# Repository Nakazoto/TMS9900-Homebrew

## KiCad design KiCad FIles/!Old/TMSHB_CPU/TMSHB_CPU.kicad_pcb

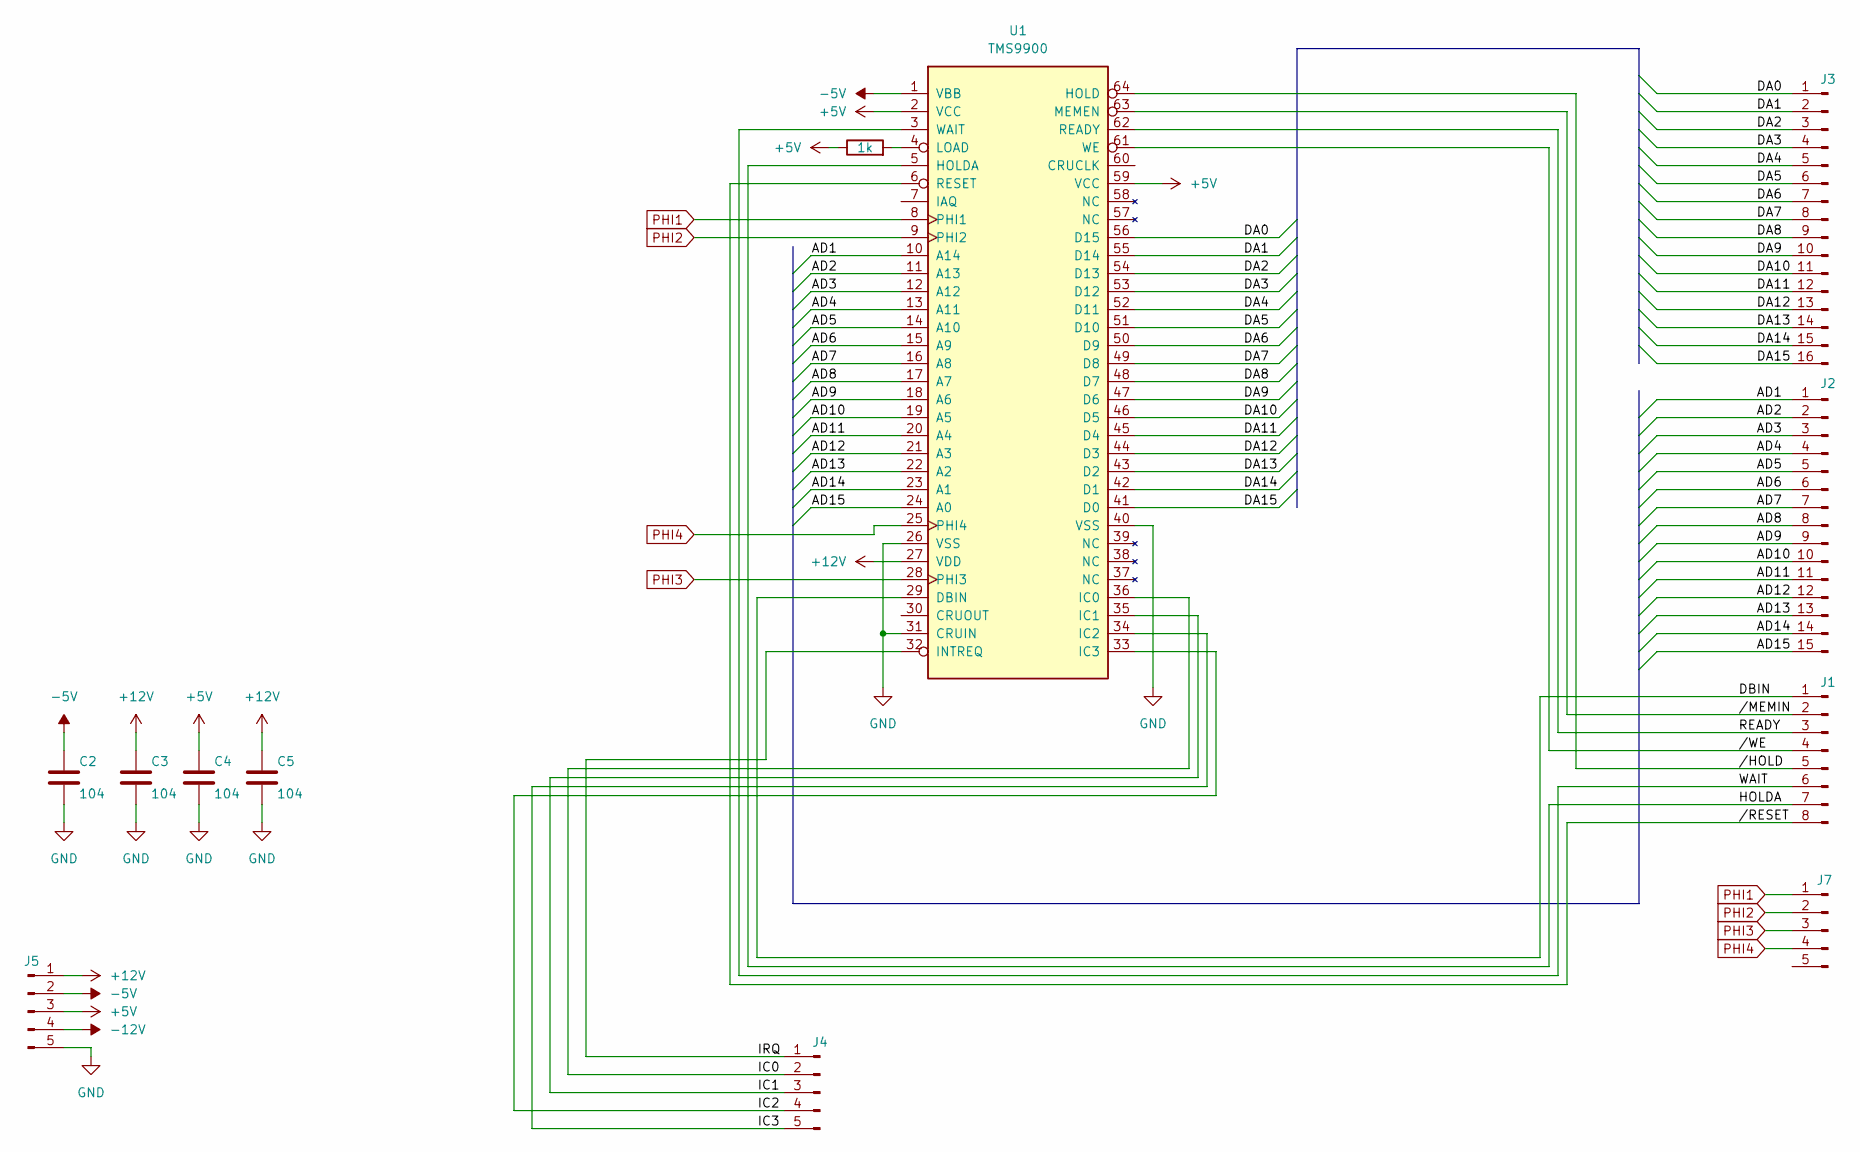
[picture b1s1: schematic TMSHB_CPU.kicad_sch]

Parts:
C2, C3, C4, C5: 104; C_Disc_D3.0mm_W2.0mm_P2.50mm
J1: Conn_01x08_Pin; PinHeader_1x08_P2.54mm_Vertical
J2: Conn_01x15_Pin; PinHeader_1x15_P2.54mm_Vertical
J3: Conn_01x16_Pin; PinHeader_1x16_P2.54mm_Vertical
J4, J5, J7: Conn_01x05_Pin; PinHeader_1x05_P2.54mm_Vertical
R1: 1k; R_Axial_DIN0207_L6.3mm_D2.5mm_P10.16mm_Horizontal
U1: TMS9900; DIP-64_W22.86mm

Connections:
+5V: C4.1, J5.3, R1.1, U1.2 (VCC), U1.59 (VCC)
+12V: C3.1, C5.1, J5.1, U1.27 (VDD)
-5V: C2.1, J5.2, U1.1 (VBB)
-12V: J5.4
/AD1: J2.1, U1.10 (A14)
/AD2: J2.2, U1.11 (A13)
/AD3: J2.3, U1.12 (A12)
/AD4: J2.4, U1.13 (A11)
/AD5: J2.5, U1.14 (A10)
/AD6: J2.6, U1.15 (A9)
/AD7: J2.7, U1.16 (A8)
/AD8: J2.8, U1.17 (A7)
/AD9: J2.9, U1.18 (A6)
/AD10: J2.10, U1.19 (A5)
/AD11: J2.11, U1.20 (A4)
/AD12: J2.12, U1.21 (A3)
/AD13: J2.13, U1.22 (A2)
/AD14: J2.14, U1.23 (A1)
/AD15: J2.15, U1.24 (A0)
/DA0: J3.1, U1.56 (D15)
/DA1: J3.2, U1.55 (D14)
/DA2: J3.3, U1.54 (D13)
/DA3: J3.4, U1.53 (D12)
/DA4: J3.5, U1.52 (D11)
/DA5: J3.6, U1.51 (D10)
/DA6: J3.7, U1.50 (D9)
/DA7: J3.8, U1.49 (D8)
/DA8: J3.9, U1.48 (D7)
/DA9: J3.10, U1.47 (D6)
/DA10: J3.11, U1.46 (D5)
/DA11: J3.12, U1.45 (D4)
/DA12: J3.13, U1.44 (D3)
/DA13: J3.14, U1.43 (D2)
/DA14: J3.15, U1.42 (D1)
/DA15: J3.16, U1.41 (D0)
/DBIN: J1.1, U1.29 (DBIN)
/HOLDA: J1.7, U1.5 (HOLDA)
/IC0: J4.2, U1.36 (IC0)
/IC1: J4.3, U1.35 (IC1)
/IC2: J4.4, U1.33 (IC3)
/IC3: J4.5, U1.34 (IC2)
/IRQ: J4.1, U1.32 (INTREQ)
/READY: J1.3, U1.62 (READY)
/WAIT: J1.6, U1.3 (WAIT)
//HOLD: J1.5, U1.64 (HOLD)
//MEMIN: J1.2, U1.63 (MEMEN)
//RESET: J1.8, U1.6 (RESET)
//WE: J1.4, U1.61 (WE)
GND: C2.2, C3.2, C4.2, C5.2, J5.5, U1.26 (VSS), U1.31 (CRUIN), U1.40 (VSS)
unnamed: R1.2, U1.4 (LOAD)
PHI1: J7.1, U1.8 (PHI1)
PHI2: J7.2, U1.9 (PHI2)
PHI3: J7.3, U1.28 (PHI3)
PHI4: J7.4, U1.25 (PHI4)

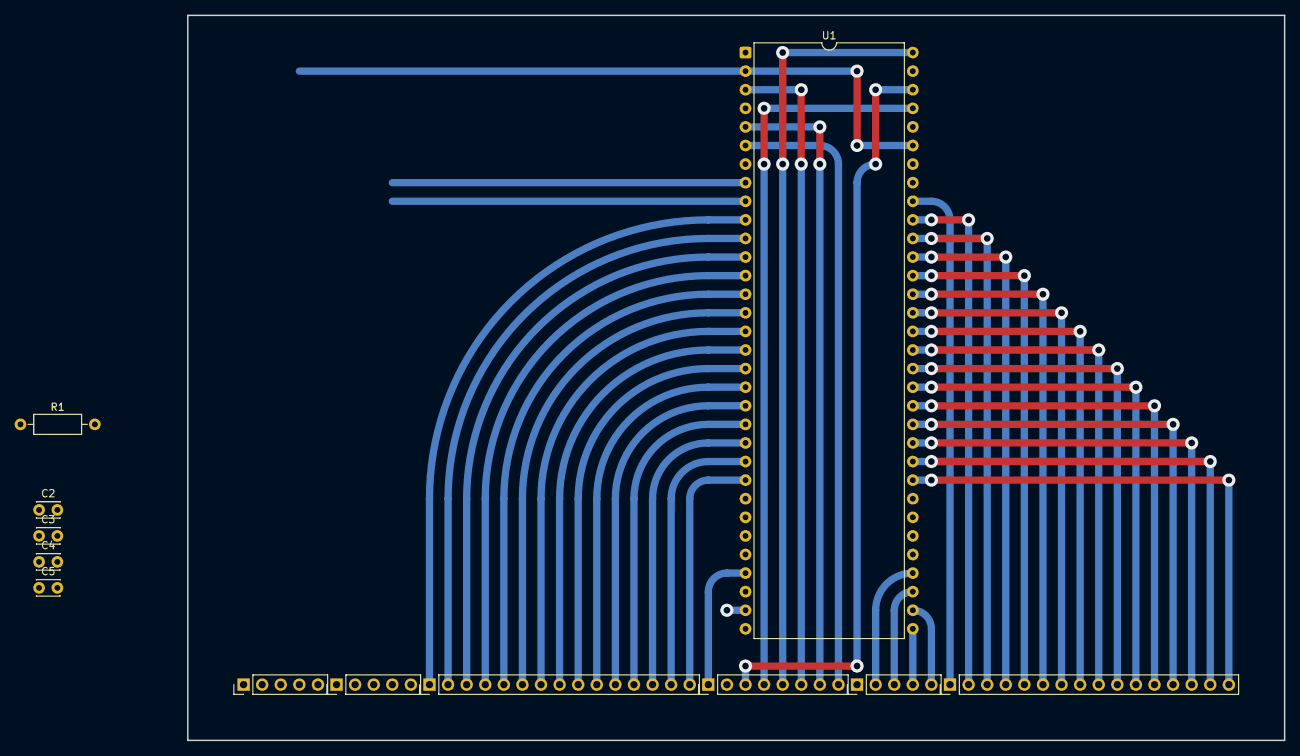
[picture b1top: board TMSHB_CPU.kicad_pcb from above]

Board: 2 copper layers, 149.9 x 99.1 mm, 12 parts (0 on the bottom side), 53 nets.

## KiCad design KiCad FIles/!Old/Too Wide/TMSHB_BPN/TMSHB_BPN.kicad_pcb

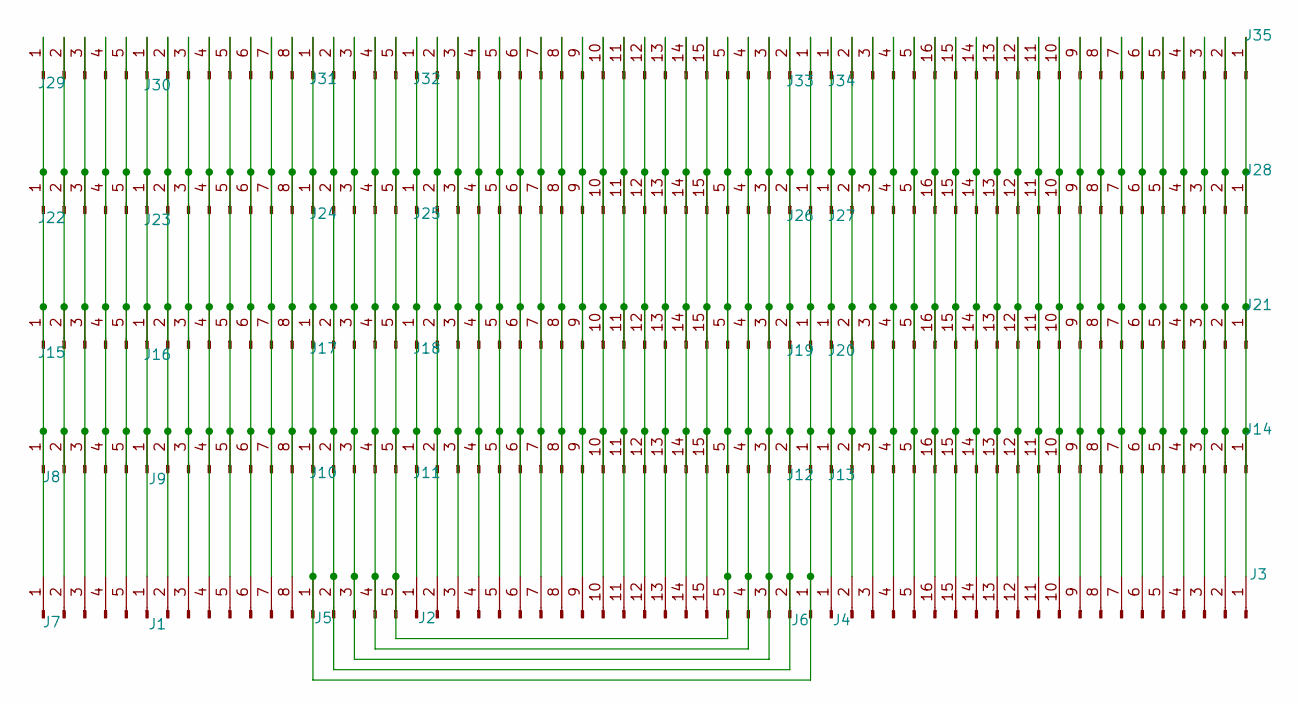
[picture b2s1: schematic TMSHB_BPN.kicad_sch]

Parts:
J1, J9, J16, J23, J30: Conn_01x08_Pin; PinHeader_1x08_P2.54mm_Vertical
J2, J11, J18, J25, J32: Conn_01x15_Pin; PinHeader_1x15_P2.54mm_Vertical
J3, J14, J21, J28, J35: Conn_01x16_Pin; PinHeader_1x16_P2.54mm_Vertical
J4, J5, J6, J7, J8, J10, J12, J13, J15, J17, J19, J20, J22, J24, J26, J27, J29, J31, J33, J34: Conn_01x05_Pin; PinHeader_1x05_P2.54mm_Vertical

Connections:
unnamed: J1.1, J9.1, J16.1, J23.1, J30.1
unnamed: J1.2, J9.2, J16.2, J23.2, J30.2
unnamed: J1.3, J9.3, J16.3, J23.3, J30.3
unnamed: J1.4, J9.4, J16.4, J23.4, J30.4
unnamed: J1.5, J9.5, J16.5, J23.5, J30.5
unnamed: J1.6, J9.6, J16.6, J23.6, J30.6
unnamed: J1.7, J9.7, J16.7, J23.7, J30.7
unnamed: J1.8, J9.8, J16.8, J23.8, J30.8
unnamed: J5.1, J6.1, J10.1, J12.1, J17.1, J19.1, J24.1, J26.1, J31.1, J33.1
unnamed: J5.2, J6.2, J10.2, J12.2, J17.2, J19.2, J24.2, J26.2, J31.2, J33.2
unnamed: J5.3, J6.3, J10.3, J12.3, J17.3, J19.3, J24.3, J26.3, J31.3, J33.3
unnamed: J5.4, J6.4, J10.4, J12.4, J17.4, J19.4, J24.4, J26.4, J31.4, J33.4
unnamed: J5.5, J6.5, J10.5, J12.5, J17.5, J19.5, J24.5, J26.5, J31.5, J33.5
unnamed: J2.1, J11.1, J18.1, J25.1, J32.1
unnamed: J2.2, J11.2, J18.2, J25.2, J32.2
unnamed: J2.3, J11.3, J18.3, J25.3, J32.3
unnamed: J2.4, J11.4, J18.4, J25.4, J32.4
unnamed: J2.5, J11.5, J18.5, J25.5, J32.5
unnamed: J2.6, J11.6, J18.6, J25.6, J32.6
unnamed: J2.7, J11.7, J18.7, J25.7, J32.7
unnamed: J2.8, J11.8, J18.8, J25.8, J32.8
unnamed: J2.9, J11.9, J18.9, J25.9, J32.9
unnamed: J2.10, J11.10, J18.10, J25.10, J32.10
unnamed: J2.11, J11.11, J18.11, J25.11, J32.11
unnamed: J2.12, J11.12, J18.12, J25.12, J32.12
unnamed: J2.13, J11.13, J18.13, J25.13, J32.13
unnamed: J2.14, J11.14, J18.14, J25.14, J32.14
unnamed: J2.15, J11.15, J18.15, J25.15, J32.15
unnamed: J4.1, J13.1, J20.1, J27.1, J34.1
unnamed: J4.2, J13.2, J20.2, J27.2, J34.2
unnamed: J4.3, J13.3, J20.3, J27.3, J34.3
unnamed: J4.4, J13.4, J20.4, J27.4, J34.4
unnamed: J4.5, J13.5, J20.5, J27.5, J34.5
unnamed: J3.1, J14.1, J21.1, J28.1, J35.1
unnamed: J3.2, J14.2, J21.2, J28.2, J35.2
unnamed: J3.3, J14.3, J21.3, J28.3, J35.3
unnamed: J3.4, J14.4, J21.4, J28.4, J35.4
unnamed: J3.5, J14.5, J21.5, J28.5, J35.5
unnamed: J3.6, J14.6, J21.6, J28.6, J35.6
unnamed: J3.7, J14.7, J21.7, J28.7, J35.7
unnamed: J3.8, J14.8, J21.8, J28.8, J35.8
unnamed: J3.9, J14.9, J21.9, J28.9, J35.9
unnamed: J3.10, J14.10, J21.10, J28.10, J35.10
unnamed: J3.11, J14.11, J21.11, J28.11, J35.11
unnamed: J3.12, J14.12, J21.12, J28.12, J35.12
unnamed: J3.13, J14.13, J21.13, J28.13, J35.13
unnamed: J3.14, J14.14, J21.14, J28.14, J35.14
unnamed: J3.15, J14.15, J21.15, J28.15, J35.15
unnamed: J3.16, J14.16, J21.16, J28.16, J35.16
unnamed: J7.1, J8.1, J15.1, J22.1, J29.1
unnamed: J7.2, J8.2, J15.2, J22.2, J29.2
unnamed: J7.3, J8.3, J15.3, J22.3, J29.3
unnamed: J7.4, J8.4, J15.4, J22.4, J29.4
unnamed: J7.5, J8.5, J15.5, J22.5, J29.5

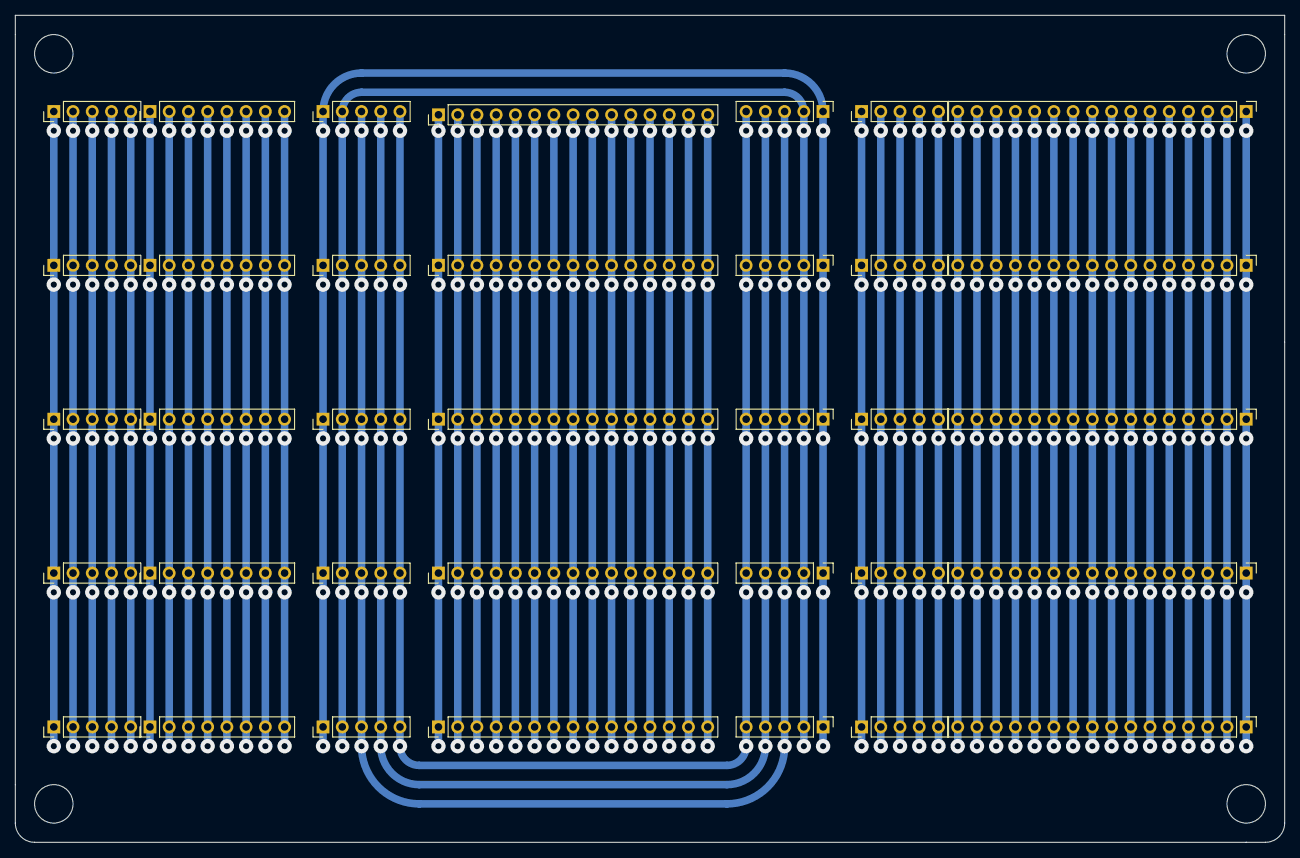
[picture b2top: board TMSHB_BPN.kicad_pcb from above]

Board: 2 copper layers, 167.6 x 109.2 mm, 35 parts (0 on the bottom side), 54 nets.

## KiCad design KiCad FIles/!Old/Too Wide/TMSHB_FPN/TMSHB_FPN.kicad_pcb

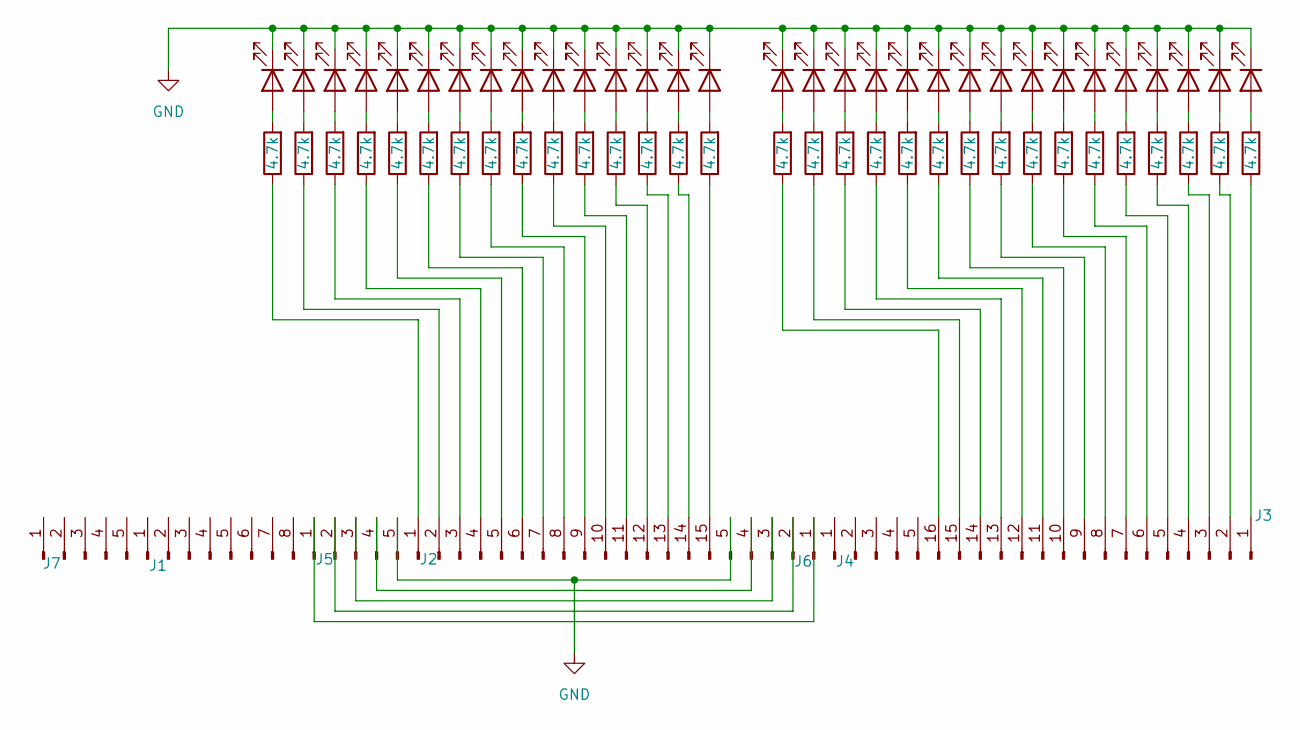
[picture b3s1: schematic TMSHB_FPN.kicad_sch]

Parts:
D1, D2, D3, D4, D5, D6, D7, D8, D9, D10, D11, D12, D13, D14, D15, D16, D18, D19, D20, D21, D22, D23, D24, D25, D26, D27, D28, D29, D30, D31, D32: LED; LED_D5.0mm
J1: Conn_01x08_Pin; PinHeader_1x08_P2.54mm_Vertical
J2: Conn_01x15_Pin; PinHeader_1x15_P2.54mm_Vertical
J3: Conn_01x16_Pin; PinHeader_1x16_P2.54mm_Vertical
J4, J5, J6, J7: Conn_01x05_Pin; PinHeader_1x05_P2.54mm_Vertical
R8, R9, R10, R11, R12, R13, R14, R15, R16, R17, R18, R19, R20, R21, R22, R23, R24, R25, R26, R27, R28, R29, R30, R31, R32, R33, R34, R35, R37, R38, R39: 4.7k; R_Axial_DIN0207_L6.3mm_D2.5mm_P10.16mm_Horizontal

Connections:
GND: D1.1 (K), D2.1 (K), D3.1 (K), D4.1 (K), D5.1 (K), D6.1 (K), D7.1 (K), D8.1 (K), D9.1 (K), D10.1 (K), D11.1 (K), D12.1 (K), D13.1 (K), D14.1 (K), D15.1 (K), D16.1 (K), D18.1 (K), D19.1 (K), D20.1 (K), D21.1 (K), D22.1 (K), D23.1 (K), D24.1 (K), D25.1 (K), D26.1 (K), D27.1 (K), D28.1 (K), D29.1 (K), D30.1 (K), D31.1 (K), D32.1 (K), J5.5, J6.5
unnamed: D1.2 (A), R8.2
unnamed: D2.2 (A), R9.2
unnamed: D3.2 (A), R11.2
unnamed: D4.2 (A), R10.2
unnamed: D5.2 (A), R17.2
unnamed: D6.2 (A), R12.2
unnamed: D7.2 (A), R15.2
unnamed: D8.2 (A), R16.2
unnamed: D9.2 (A), R27.2
unnamed: D10.2 (A), R18.2
unnamed: D11.2 (A), R19.2
unnamed: D12.2 (A), R20.2
unnamed: D13.2 (A), R21.2
unnamed: D14.2 (A), R22.2
unnamed: D15.2 (A), R13.2
unnamed: D16.2 (A), R14.2
unnamed: D18.2 (A), R37.2
unnamed: D19.2 (A), R38.2
unnamed: D20.2 (A), R39.2
unnamed: D21.2 (A), R32.2
unnamed: D22.2 (A), R33.2
unnamed: D23.2 (A), R34.2
unnamed: D24.2 (A), R35.2
unnamed: D25.2 (A), R28.2
unnamed: D26.2 (A), R29.2
unnamed: D27.2 (A), R30.2
unnamed: D28.2 (A), R31.2
unnamed: D29.2 (A), R23.2
unnamed: D30.2 (A), R24.2
unnamed: D31.2 (A), R25.2
unnamed: D32.2 (A), R26.2
unnamed: J2.1, R37.1
unnamed: J2.2, R38.1
unnamed: J2.3, R39.1
unnamed: J2.4, R32.1
unnamed: J2.5, R33.1
unnamed: J2.6, R34.1
unnamed: J2.7, R35.1
unnamed: J2.8, R28.1
unnamed: J2.9, R29.1
unnamed: J2.10, R30.1
unnamed: J2.11, R31.1
unnamed: J2.12, R23.1
unnamed: J2.13, R24.1
unnamed: J2.14, R25.1
unnamed: J2.15, R26.1
unnamed: J3.1, R8.1
unnamed: J3.2, R9.1
unnamed: J3.3, R10.1
unnamed: J3.4, R11.1
unnamed: J3.5, R12.1
unnamed: J3.6, R17.1
unnamed: J3.7, R16.1
unnamed: J3.8, R15.1
unnamed: J3.9, R14.1
unnamed: J3.10, R13.1
unnamed: J3.11, R22.1
unnamed: J3.12, R21.1
unnamed: J3.13, R20.1
unnamed: J3.14, R19.1
unnamed: J3.15, R18.1
unnamed: J3.16, R27.1
unnamed: J5.1, J6.1
unnamed: J5.2, J6.2
unnamed: J5.3, J6.3
unnamed: J5.4, J6.4

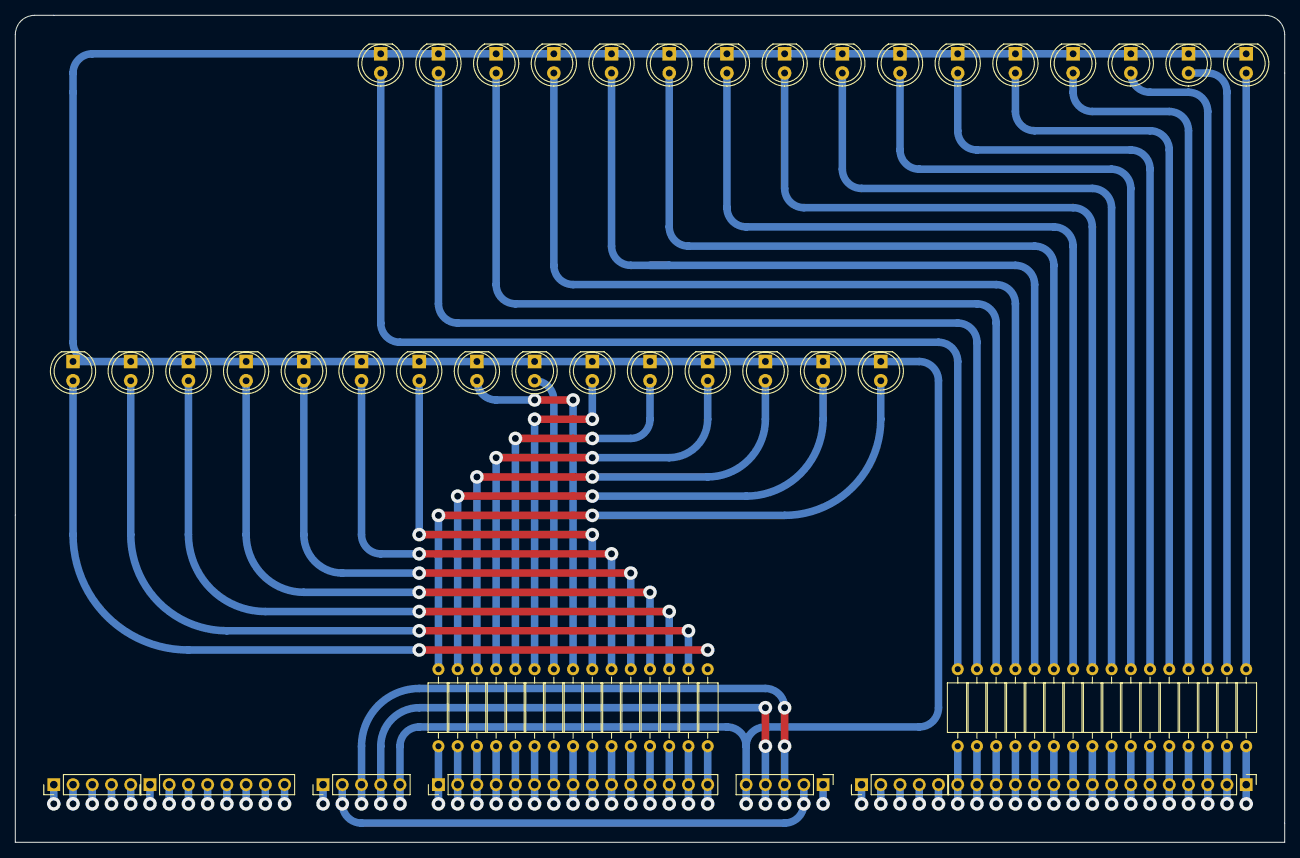
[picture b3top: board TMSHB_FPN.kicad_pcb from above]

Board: 2 copper layers, 167.6 x 109.2 mm, 69 parts (0 on the bottom side), 67 nets.

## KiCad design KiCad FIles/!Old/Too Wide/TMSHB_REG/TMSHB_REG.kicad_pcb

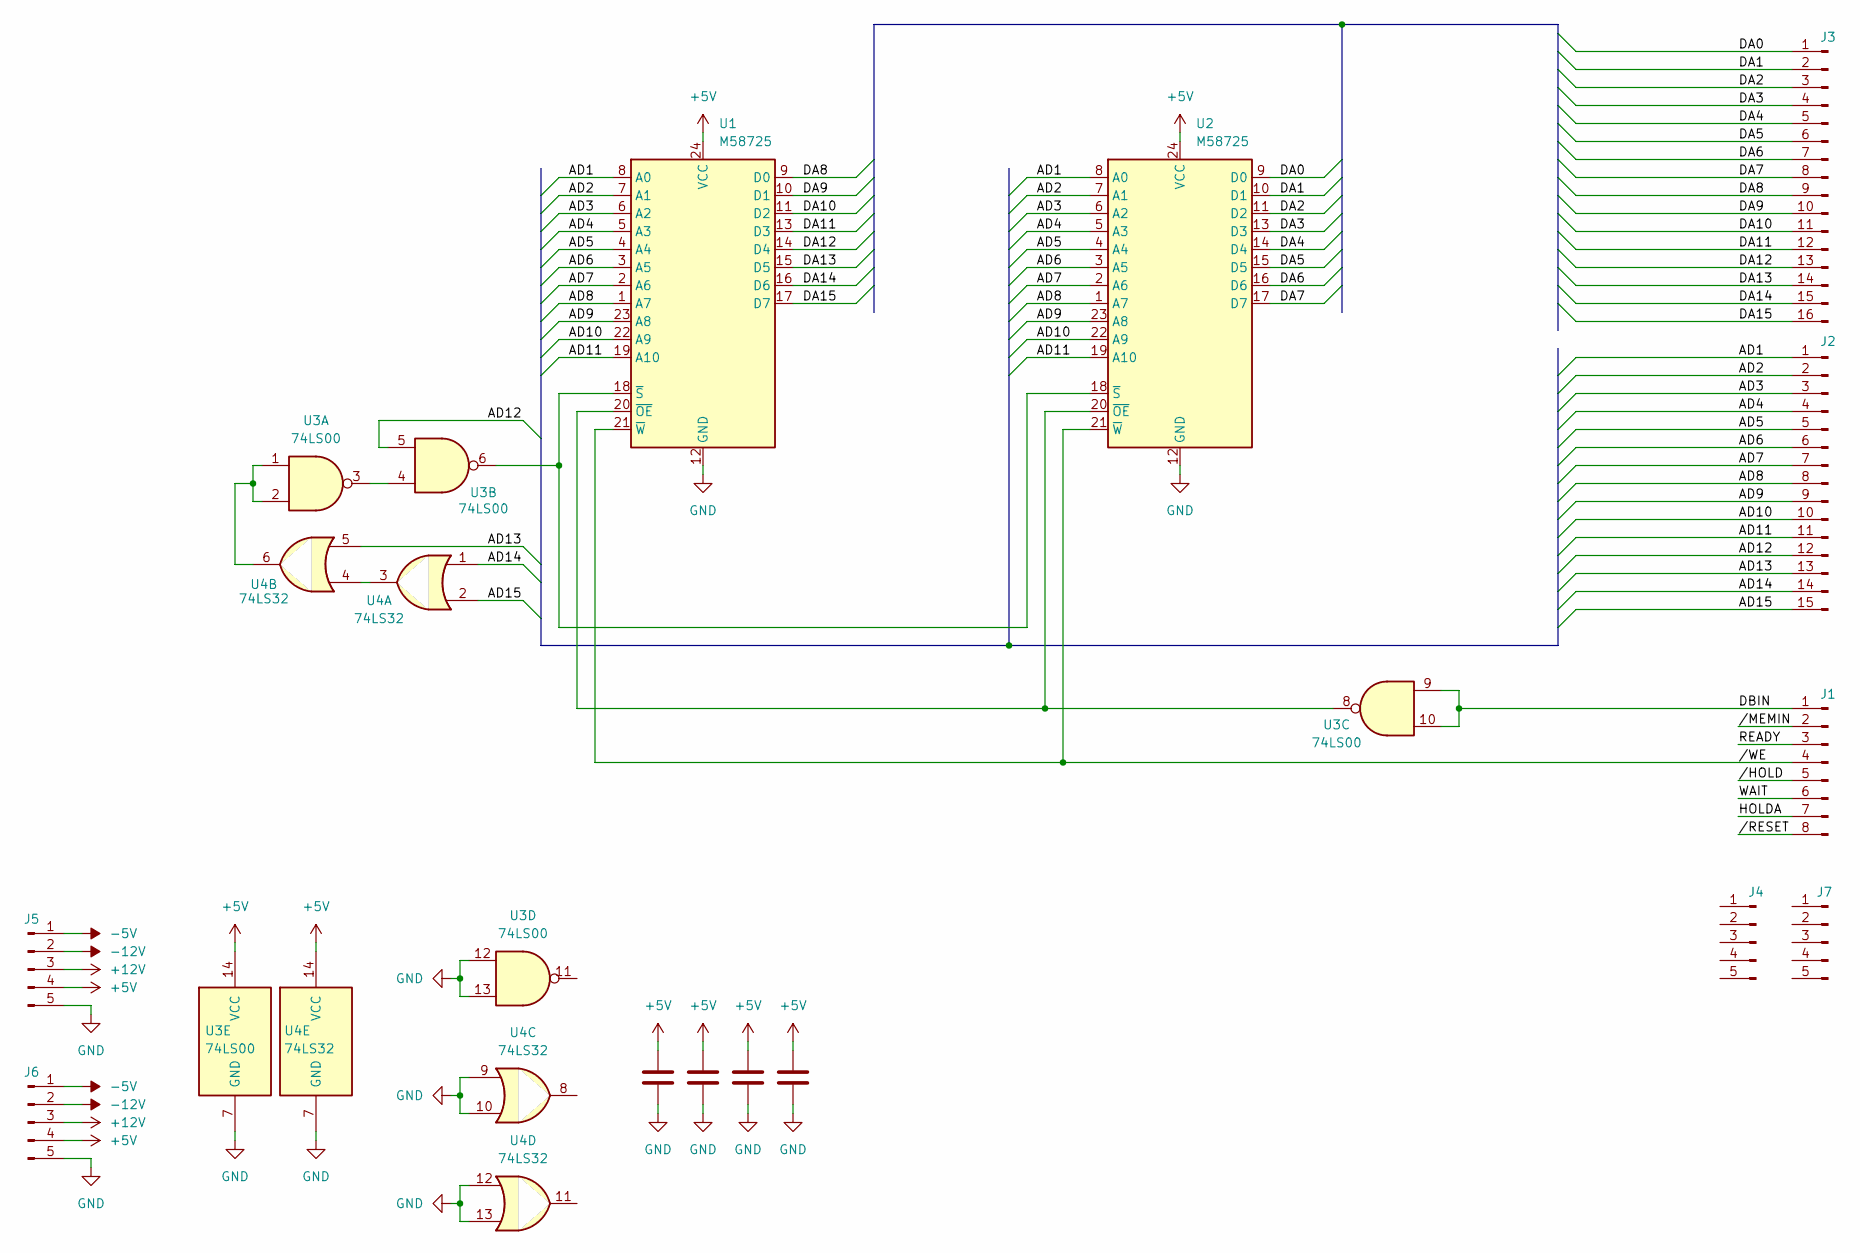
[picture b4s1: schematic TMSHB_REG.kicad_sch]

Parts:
C1, C2, C3, C4: C; C_Disc_D3.0mm_W1.6mm_P2.50mm
J1: Conn_01x08_Pin; PinHeader_1x08_P2.54mm_Vertical
J2: Conn_01x15_Pin; PinHeader_1x15_P2.54mm_Vertical
J3: Conn_01x16_Pin; PinHeader_1x16_P2.54mm_Vertical
J4, J5, J6, J7: Conn_01x05_Pin; PinHeader_1x05_P2.54mm_Vertical
U1, U2: M58725; DIP-24_18.0mmx34.29mm_W15.24mm
U3: 74LS00; DIP-14_W7.62mm
U4: 74LS32; DIP-14_W7.62mm

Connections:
+5V: C1.1, C2.1, C3.1, C4.1, J5.4, J6.4, U1.24 (VCC), U2.24 (VCC), U3.14 (VCC), U4.14 (VCC)
+12V: J5.3, J6.3
-5V: J5.1, J6.1
-12V: J5.2, J6.2
/AD1: J2.1, U1.8 (A0), U2.8 (A0)
/AD2: J2.2, U1.7 (A1), U2.7 (A1)
/AD3: J2.3, U1.6 (A2), U2.6 (A2)
/AD4: J2.4, U1.5 (A3), U2.5 (A3)
/AD5: J2.5, U1.4 (A4), U2.4 (A4)
/AD6: J2.6, U1.3 (A5), U2.3 (A5)
/AD7: J2.7, U1.2 (A6), U2.2 (A6)
/AD8: J2.8, U1.1 (A7), U2.1 (A7)
/AD9: J2.9, U1.23 (A8), U2.23 (A8)
/AD10: J2.10, U1.22 (A9), U2.22 (A9)
/AD11: J2.11, U1.19 (A10), U2.19 (A10)
/AD12: J2.12, U3.5
/AD13: J2.13, U4.5
/AD14: J2.14, U4.1
/AD15: J2.15, U4.2
/DA0: J3.1, U2.9 (D0)
/DA1: J3.2, U2.10 (D1)
/DA2: J3.3, U2.11 (D2)
/DA3: J3.4, U2.13 (D3)
/DA4: J3.5, U2.14 (D4)
/DA5: J3.6, U2.15 (D5)
/DA6: J3.7, U2.16 (D6)
/DA7: J3.8, U2.17 (D7)
/DA8: J3.9, U1.9 (D0)
/DA9: J3.10, U1.10 (D1)
/DA10: J3.11, U1.11 (D2)
/DA11: J3.12, U1.13 (D3)
/DA12: J3.13, U1.14 (D4)
/DA13: J3.14, U1.15 (D5)
/DA14: J3.15, U1.16 (D6)
/DA15: J3.16, U1.17 (D7)
/DBIN: J1.1, U3.9, U3.10
/HOLDA: J1.7
/READY: J1.3
/WAIT: J1.6
//HOLD: J1.5
//MEMIN: J1.2
//RESET: J1.8
//WE: J1.4, U1.21 (~W), U2.21 (~W)
GND: C1.2, C2.2, C3.2, C4.2, J5.5, J6.5, U1.12 (GND), U2.12 (GND), U3.7 (GND), U3.12, U3.13, U4.7 (GND), U4.9, U4.10, U4.12, U4.13
unnamed: U1.20 (~OE), U2.20 (~OE), U3.8
unnamed: U1.18 (~S), U2.18 (~S), U3.6
unnamed: U3.1, U3.2, U4.6
unnamed: U3.3, U3.4
unnamed: U4.3, U4.4

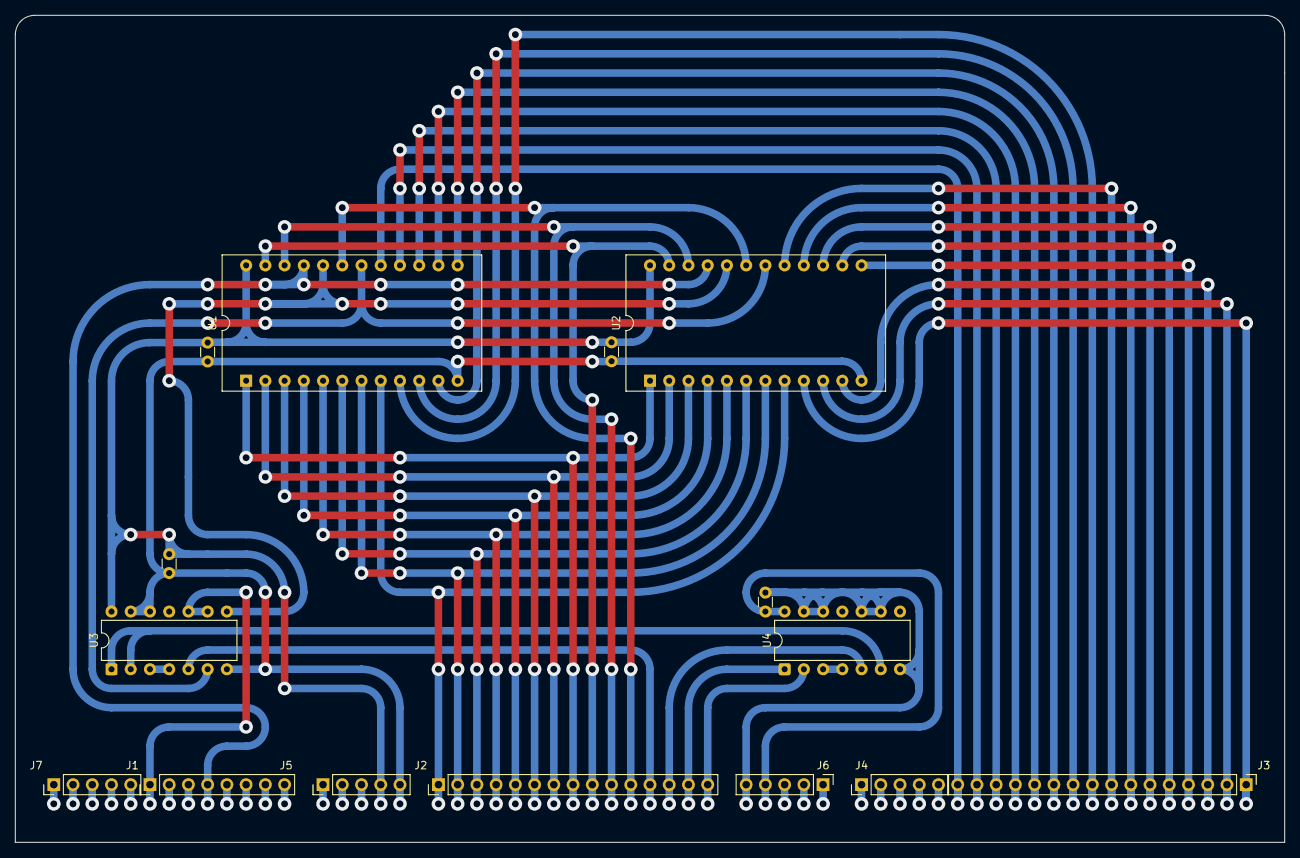
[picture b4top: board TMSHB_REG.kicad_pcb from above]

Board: 2 copper layers, 167.6 x 109.2 mm, 15 parts (0 on the bottom side), 43 nets.

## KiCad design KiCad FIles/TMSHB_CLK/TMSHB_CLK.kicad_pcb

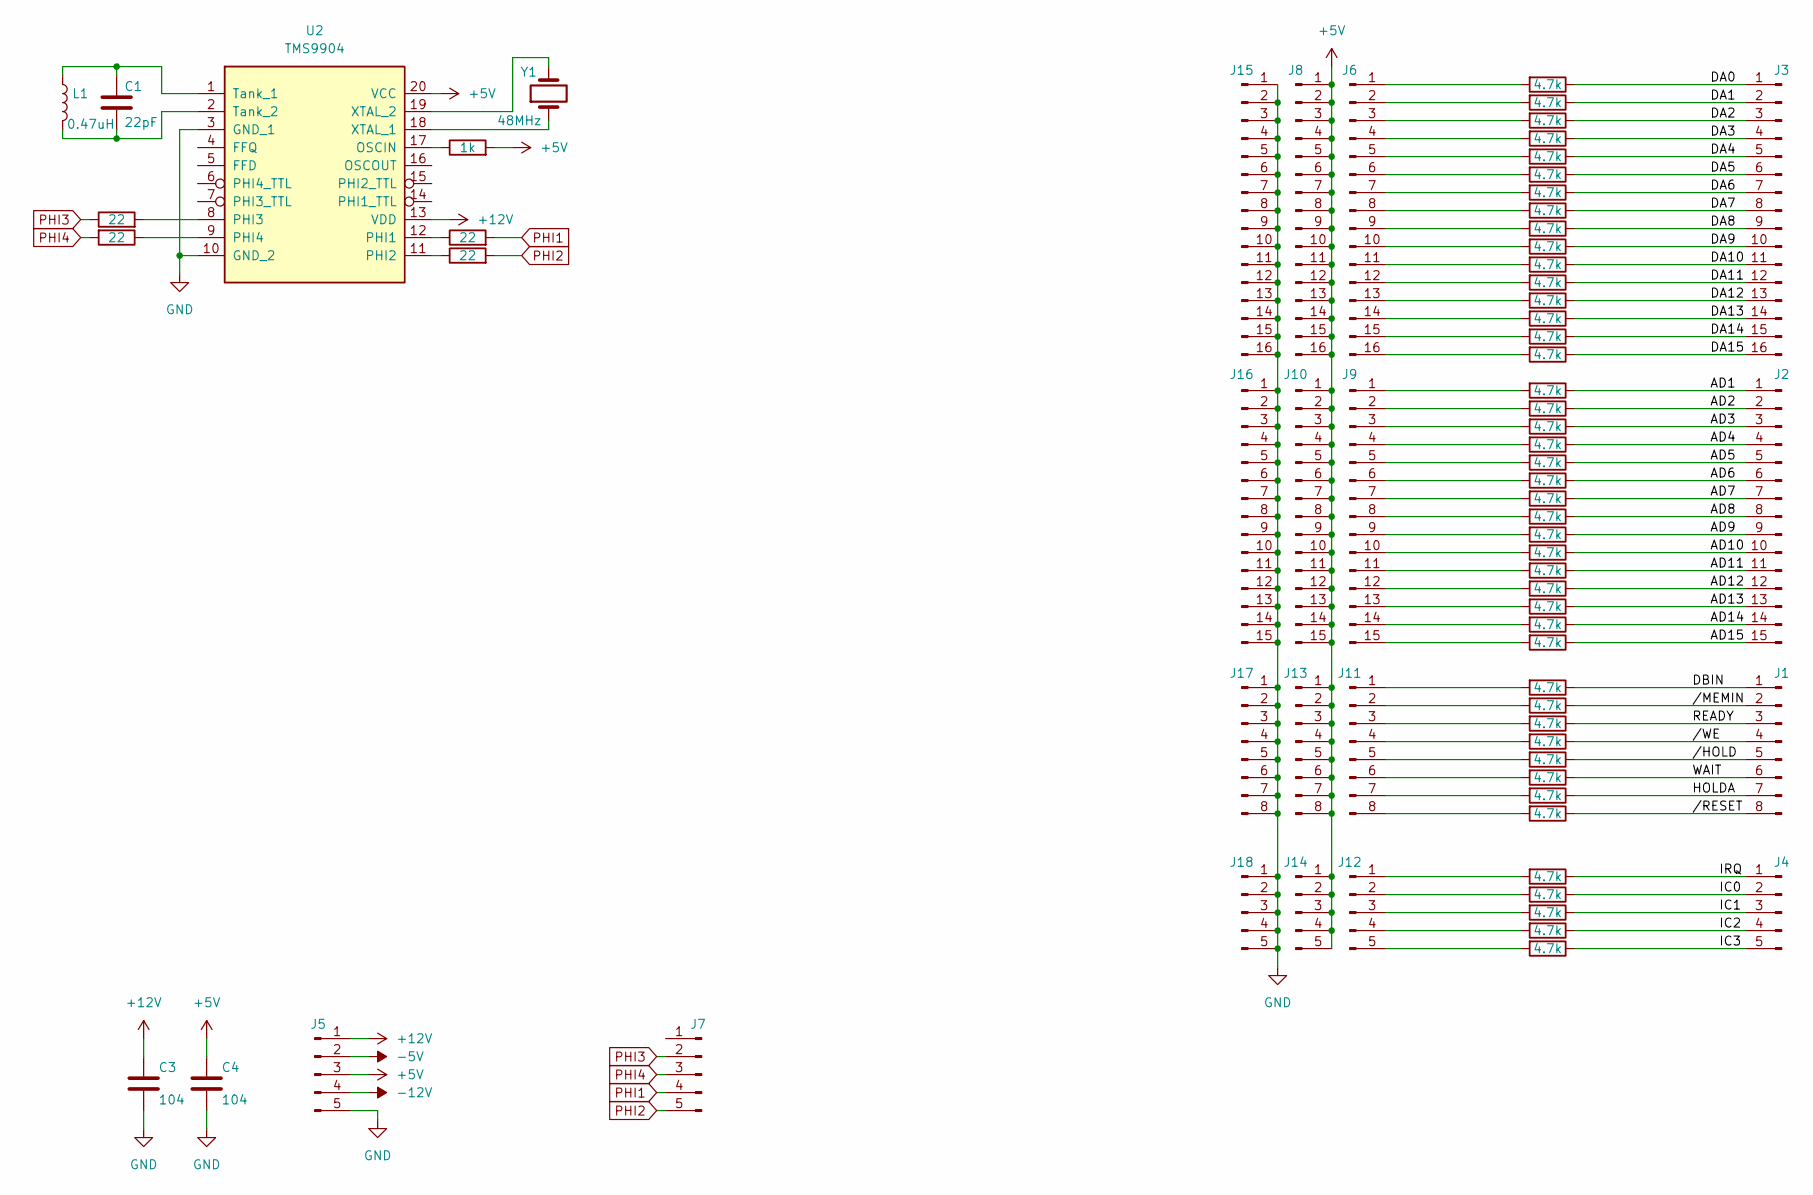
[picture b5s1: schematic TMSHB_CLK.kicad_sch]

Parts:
C1: 22pF; C_Disc_D3.0mm_W2.0mm_P2.50mm
C3, C4: 104; C_Disc_D3.0mm_W2.0mm_P2.50mm
J1, J11, J13, J17: Conn_01x08_Pin; PinHeader_1x08_P2.54mm_Vertical
J2, J9, J10, J16: Conn_01x15_Pin; PinHeader_1x15_P2.54mm_Vertical
J3, J6, J8, J15: Conn_01x16_Pin; PinHeader_1x16_P2.54mm_Vertical
J4, J5, J7, J12, J14, J18: Conn_01x05_Pin; PinHeader_1x05_P2.54mm_Vertical
L1: 0.47uH; L_Axial_L6.6mm_D2.7mm_P10.16mm_Horizontal_Vishay_IM-2
R3, R4, R5, R6: 22; R_Axial_DIN0207_L6.3mm_D2.5mm_P10.16mm_Horizontal
R7: 1k; R_Axial_DIN0207_L6.3mm_D2.5mm_P10.16mm_Horizontal
R13, R14, R15, R16, R17, R18, R19, R20, R21, R22, R23, R24, R25, R26, R27, R28, R29, R30, R31, R32, R33, R34, R35, R36, R37, R38, R39, R40, R41, R42, R43, R44, R45, R46, R47, R48, R49, R50, R51, R52, R53, R54, R55, R56: 4.7k; R_Axial_DIN0207_L6.3mm_D2.5mm_P10.16mm_Horizontal
U2: TMS9904; DIP-20_W7.62mm
Y1: 48MHz; Crystal_HC52-U_Vertical

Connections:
+5V: C4.1, J5.3, J8.1, J8.2, J8.3, J8.4, J8.5, J8.6, J8.7, J8.8, J8.9, J8.10, J8.11, J8.12, J8.13, J8.14, J8.15, J8.16, J10.1, J10.2, J10.3, J10.4, J10.5, J10.6, J10.7, J10.8, J10.9, J10.10, J10.11, J10.12, J10.13, J10.14, J10.15, J13.1, J13.2, J13.3, J13.4, J13.5, J13.6, J13.7, J13.8, J14.1, J14.2, J14.3, J14.4, J14.5, R7.2, U2.20 (VCC)
+12V: C3.1, J5.1, U2.13 (VDD)
-5V: J5.2
-12V: J5.4
/AD1: J2.1, R28.1
/AD2: J2.2, R29.1
/AD3: J2.3, R30.1
/AD4: J2.4, R31.1
/AD5: J2.5, R32.1
/AD6: J2.6, R33.1
/AD7: J2.7, R34.1
/AD8: J2.8, R35.1
/AD9: J2.9, R36.1
/AD10: J2.10, R37.1
/AD11: J2.11, R38.1
/AD12: J2.12, R39.1
/AD13: J2.13, R40.1
/AD14: J2.14, R41.1
/AD15: J2.15, R42.1
/DA0: J3.1, R13.1
/DA1: J3.2, R14.1
/DA2: J3.3, R15.1
/DA3: J3.4, R16.1
/DA4: J3.5, R17.1
/DA5: J3.6, R18.1
/DA6: J3.7, R19.1
/DA7: J3.8, R20.1
/DA8: J3.9, R21.1
/DA9: J3.10, R22.1
/DA10: J3.11, R23.1
/DA11: J3.12, R24.1
/DA12: J3.13, R25.1
/DA13: J3.14, R26.1
/DA14: J3.15, R27.1
/DA15: J3.16, R43.1
/DBIN: J1.1, R44.1
/HOLDA: J1.7, R50.1
/IC0: J4.2, R53.1
/IC1: J4.3, R54.1
/IC2: J4.4, R55.1
/IC3: J4.5, R56.1
/IRQ: J4.1, R52.1
/READY: J1.3, R46.1
/WAIT: J1.6, R49.1
//HOLD: J1.5, R48.1
//MEMIN: J1.2, R45.1
//RESET: J1.8, R51.1
//WE: J1.4, R47.1
GND: C3.2, C4.2, J5.5, J15.1, J15.2, J15.3, J15.4, J15.5, J15.6, J15.7, J15.8, J15.9, J15.10, J15.11, J15.12, J15.13, J15.14, J15.15, J15.16, J16.1, J16.2, J16.3, J16.4, J16.5, J16.6, J16.7, J16.8, J16.9, J16.10, J16.11, J16.12, J16.13, J16.14, J16.15, J17.1, J17.2, J17.3, J17.4, J17.5, J17.6, J17.7, J17.8, J18.1, J18.2, J18.3, J18.4, J18.5, U2.3 (GND_1), U2.10 (GND_2)
unnamed: J6.1, R13.2
unnamed: J6.2, R14.2
unnamed: J6.3, R15.2
unnamed: J6.4, R16.2
unnamed: J6.5, R17.2
unnamed: J6.6, R18.2
unnamed: J6.7, R19.2
unnamed: J6.8, R20.2
unnamed: J6.9, R21.2
unnamed: J6.10, R22.2
unnamed: J6.11, R23.2
unnamed: J6.12, R24.2
unnamed: J6.13, R25.2
unnamed: J6.14, R26.2
unnamed: J6.15, R27.2
unnamed: J6.16, R43.2
unnamed: J9.1, R28.2
unnamed: J9.2, R29.2
unnamed: J9.3, R30.2
unnamed: J9.4, R31.2
unnamed: J9.5, R32.2
unnamed: J9.6, R33.2
unnamed: J9.7, R34.2
unnamed: J9.8, R35.2
unnamed: J9.9, R36.2
unnamed: J9.10, R37.2
unnamed: J9.11, R38.2
unnamed: J9.12, R39.2
unnamed: J9.13, R40.2
unnamed: J9.14, R41.2
unnamed: J9.15, R42.2
unnamed: J11.1, R44.2
unnamed: J11.2, R45.2
unnamed: J11.3, R46.2
unnamed: J11.4, R47.2
unnamed: J11.5, R48.2
unnamed: J11.6, R49.2
unnamed: J11.7, R50.2
unnamed: J11.8, R51.2
unnamed: J12.1, R52.2
unnamed: J12.2, R53.2
unnamed: J12.3, R54.2
unnamed: J12.4, R55.2
unnamed: J12.5, R56.2
unnamed: R7.1, U2.17 (OSCIN)
unnamed: R3.1, U2.12 (PHI1)
unnamed: R4.1, U2.11 (PHI2)
unnamed: R6.2, U2.8 (PHI3)
unnamed: R5.1, U2.9 (PHI4)
unnamed: C1.1, L1.1, U2.1 (Tank_1)
unnamed: C1.2, L1.2, U2.2 (Tank_2)
unnamed: U2.18 (XTAL_1), Y1.1
unnamed: U2.19 (XTAL_2), Y1.2
PHI1: J7.4, R3.2
PHI2: J7.5, R4.2
PHI3: J7.2, R6.1
PHI4: J7.3, R5.2

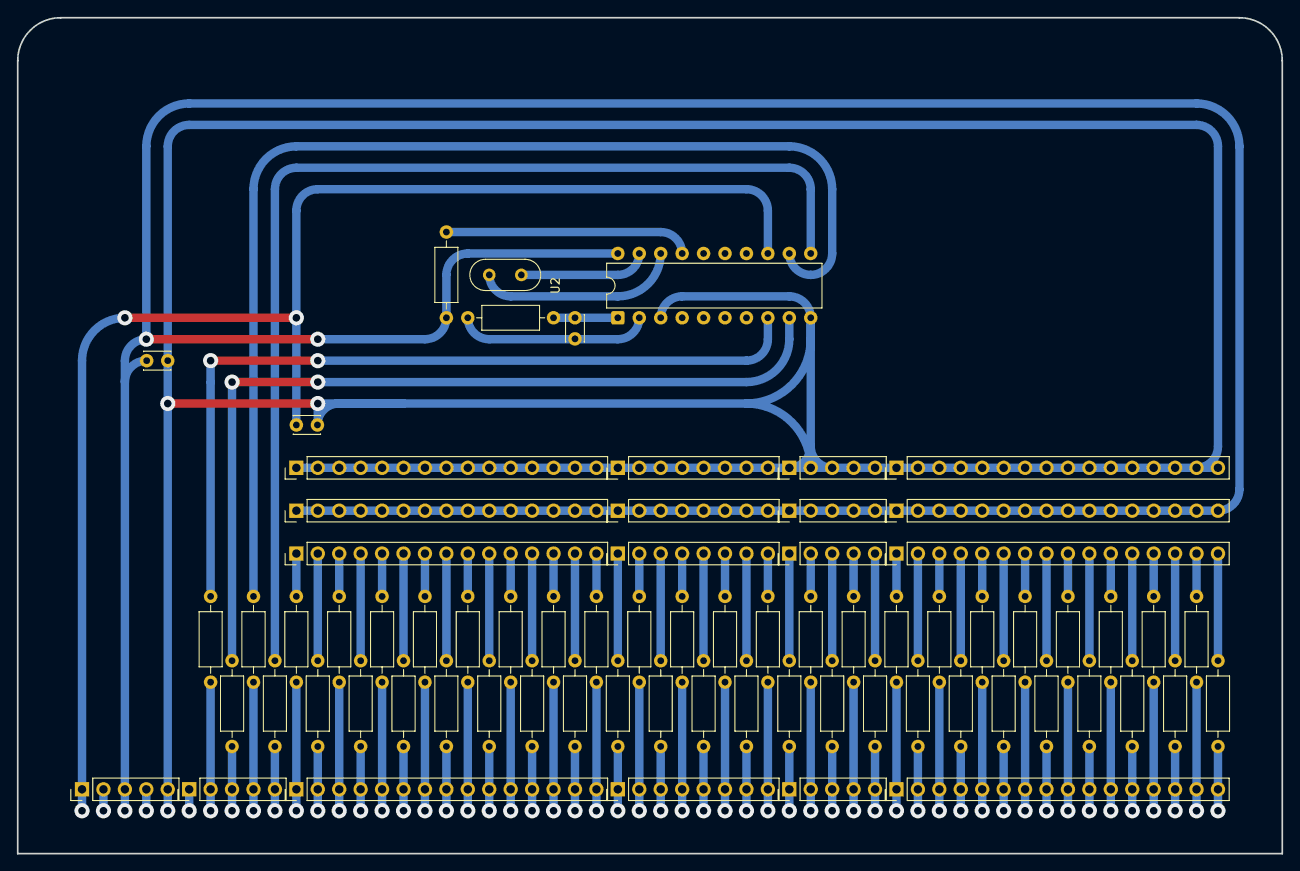
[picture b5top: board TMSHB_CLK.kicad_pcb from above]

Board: 2 copper layers, 149.9 x 99.1 mm, 73 parts (0 on the bottom side), 104 nets.
